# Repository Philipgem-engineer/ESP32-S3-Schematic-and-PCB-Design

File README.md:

# 🧠 ESP32-S3 – Schematic and PCB Design

This repository contains a custom hardware of an ESP32-S3 microcontroller dev board.
It includes the complete schematic and PCB layout, featuring essential supporting circuits.

##  Features
- ⚡ LDO Voltage Regulator – Provides a stable supply for the ESP32-S3 and peripherals
- 🔋 Battery Charging Circuit – Supports rechargeable lithium battery input
- 💾 Flash Memory – Enables program storage capacity
- 🧩 ESP32-S3 System-on-Chip – Dual-core processor with integrated Wi-Fi and Bluetooth
- ⏱️ Crystal Oscillator – Ensures precise clock timing for system stability
- 📡 Antenna & Antenna Matching Circuit – Integrated in PCB for Wi-Fi/Bluetooth connectivity

##  Tools Used
-  Schematic & PCB Design: KiCad
-  Component Library: LCSC
-  PCB Fabrication: JLCPCB

##  Schematic

##  PCB Design

##  PCB 3D view

##  Manufactured PCB

## 📁 File Structure

<details>
  <summary>ESP32-S3 Project/</summary>
  <ul>
    <li>
      Media/
      <ul>
        <li>(PDF, Images and videos of prototype)</li>
      </ul>
    </li>
    <li>
      pcb/
      <ul>
        <li>(Gerber, BOM, Positions)</li>
      </ul>
    </li>
</details>

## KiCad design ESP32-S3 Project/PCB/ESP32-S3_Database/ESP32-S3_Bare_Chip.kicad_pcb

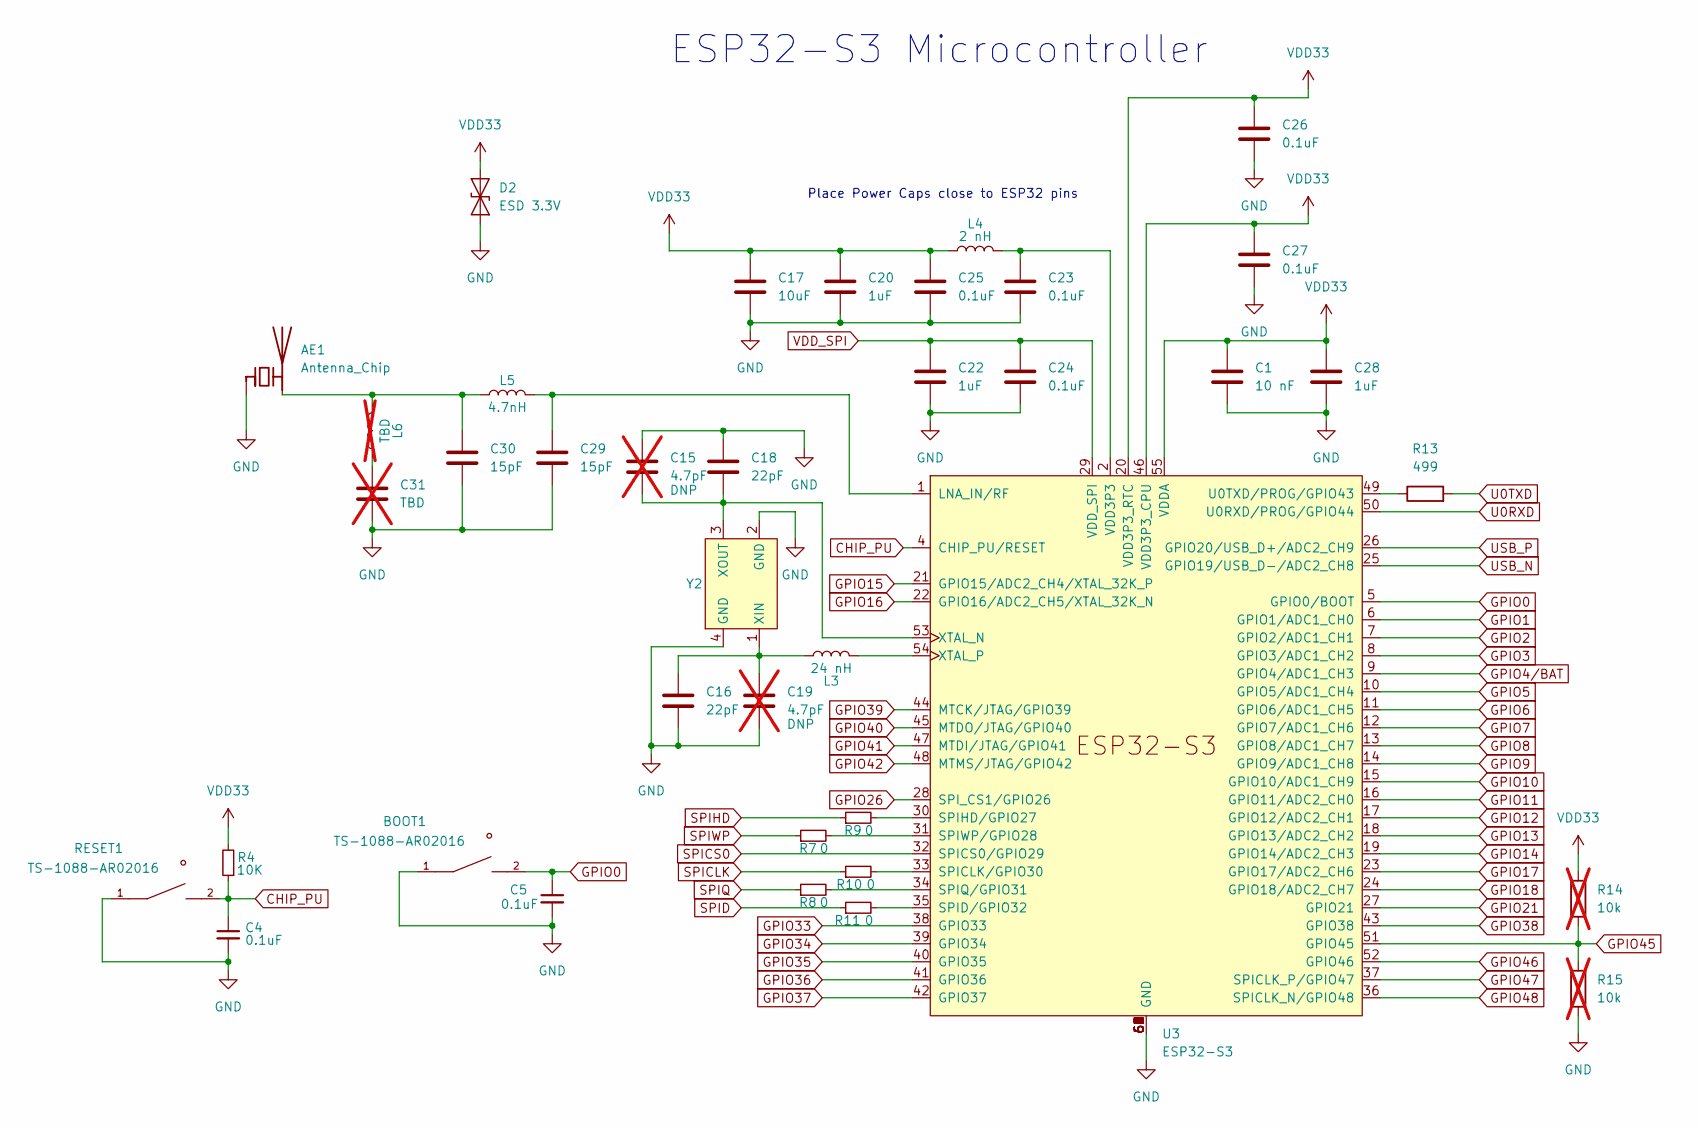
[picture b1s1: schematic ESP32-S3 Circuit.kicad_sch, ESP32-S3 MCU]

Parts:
AE1: Antenna_Chip; Texas_SWRA117D_2.4GHz_Left
BOOT1: TS-1088-AR02016; SW_TS-1088-AR02016; PARTREV N/A
C1: 10 nF; C_0402_1005Metric; MPN CL05B103KB5NNNC
C4, C5, C23, C24, C25, C26, C27: 0.1uF; C_0402_1005Metric; MPN CL05B104KO5NNNC
C15, C19: 4.7pF; C_0402_1005Metric; not fitted
C16, C18: 22pF; C_0402_1005Metric; MPN 0402CG220J500NT
C17: 10uF; C_0402_1005Metric; MPN CL05A106MQ5NUNC
C20, C22, C28: 1uF; C_0402_1005Metric; MPN CL05A105KA5NQNC
C29, C30: 15pF; C_0402_1005Metric; MPN 0402CG220J500NT
C31: TBD; C_0402_1005Metric; MPN 0402CG220J500NT; not fitted
D2: ESD 3.3V; D_SOD-323; MPN H3V3HD3B
L3: 24 nH; L_0402_1005Metric; MPN SDCL1005C24NJTDF
L4: 2 nH; L_0603_1608Metric; MPN SDCL1608C2N0STDF
L5: 4.7nH; L_0402_1005Metric; MPN SDCL1005C4N7STDF
L6: TBD; L_0402_1005Metric; not fitted
R4: 10K; R_0603_1608Metric; MPN 0603WAF1002T5E
R7, R8, R9, R10, R11: 0; R_0402_1005Metric; MPN 0402WGF0000TCE
R13: 499; R_0402_1005Metric; MPN 0402WGF4700TCE
R14, R15: 10k; R_0402_1005Metric; MPN 0402WGF1002TCE; not fitted
RESET1: TS-1088-AR02016; SW_TS-1088-AR02016; PARTREV N/A
U3: ESP32-S3; IC_ESP32-S3; MPN ESP32-S3; LCSC PN C2913192
Y2: Crystal_SMD_3225-4Pin_3.2x2.5mm; MPN 5YMA40000151SF40E1

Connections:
CHIP_PU: C4.1, R4.1, RESET1.2, U3.4 (CHIP_PU/RESET); also elsewhere on the board
GND: AE1.2 (FEED), BOOT1.1, C1.2, C4.2, C5.2, C15.1, C16.2, C17.2, C18.1, C19.2, C20.2, C22.2, C23.2, C24.2, C25.2, C26.2, C27.2, C28.2, C29.2, C30.2, C31.2, D2.1 (A1), R15.1, RESET1.1, U3.57 (GND), U3.58 (GND), U3.59 (GND), U3.60 (GND), U3.61 (GND), U3.62 (GND), U3.63 (GND), U3.64 (GND), U3.65 (GND), U3.66 (GND), U3.67 (GND), U3.68 (GND), U3.69 (GND), Y2.2 (GND), Y2.4 (GND); also elsewhere on the board
GPIO0: BOOT1.2, C5.1, U3.5 (GPIO0/BOOT); also elsewhere on the board
GPIO1: U3.6 (GPIO1/ADC1_CH0); also elsewhere on the board
GPIO2: U3.7 (GPIO2/ADC1_CH1); also elsewhere on the board
GPIO3: U3.8 (GPIO3/ADC1_CH2); also elsewhere on the board
GPIO4/BAT: U3.9 (GPIO4/ADC1_CH3); also elsewhere on the board
GPIO5: U3.10 (GPIO5/ADC1_CH4); also elsewhere on the board
GPIO6: U3.11 (GPIO6/ADC1_CH5); also elsewhere on the board
GPIO7: U3.12 (GPIO7/ADC1_CH6); also elsewhere on the board
GPIO8: U3.13 (GPIO8/ADC1_CH7); also elsewhere on the board
GPIO9: U3.14 (GPIO9/ADC1_CH8); also elsewhere on the board
GPIO10: U3.15 (GPIO10/ADC1_CH9); also elsewhere on the board
GPIO11: U3.16 (GPIO11/ADC2_CH0); also elsewhere on the board
GPIO12: U3.17 (GPIO12/ADC2_CH1); also elsewhere on the board
GPIO13: U3.18 (GPIO13/ADC2_CH2); also elsewhere on the board
GPIO14: U3.19 (GPIO14/ADC2_CH3); also elsewhere on the board
GPIO15: U3.21 (GPIO15/ADC2_CH4/XTAL_32K_P); also elsewhere on the board
GPIO16: U3.22 (GPIO16/ADC2_CH5/XTAL_32K_N); also elsewhere on the board
GPIO17: U3.23 (GPIO17/ADC2_CH6); also elsewhere on the board
GPIO18: U3.24 (GPIO18/ADC2_CH7); also elsewhere on the board
GPIO21: U3.27 (GPIO21); also elsewhere on the board
GPIO26: U3.28 (SPI_CS1/GPIO26); also elsewhere on the board
GPIO33: U3.38 (GPIO33); also elsewhere on the board
GPIO34: U3.39 (GPIO34); also elsewhere on the board
GPIO35: U3.40 (GPIO35); also elsewhere on the board
GPIO36: U3.41 (GPIO36); also elsewhere on the board
GPIO37: U3.42 (GPIO37); also elsewhere on the board
GPIO38: U3.43 (GPIO38); also elsewhere on the board
GPIO39: U3.44 (MTCK/JTAG/GPIO39); also elsewhere on the board
GPIO40: U3.45 (MTDO/JTAG/GPIO40); also elsewhere on the board
GPIO41: U3.47 (MTDI/JTAG/GPIO41); also elsewhere on the board
GPIO42: U3.48 (MTMS/JTAG/GPIO42); also elsewhere on the board
GPIO45: R14.1, R15.2, U3.51 (GPIO45); also elsewhere on the board
GPIO46: U3.52 (GPIO46); also elsewhere on the board
GPIO47: U3.37 (SPICLK_P/GPIO47); also elsewhere on the board
GPIO48: U3.36 (SPICLK_N/GPIO48); also elsewhere on the board
unnamed: AE1.1 (PCB_Trace), C30.1, L5.1, L6.2
unnamed: C31.1, L6.1
unnamed: C29.1, L5.2, U3.1 (LNA_IN/RF)
unnamed: R10.2, U3.33 (SPICLK/GPIO30)
unnamed: R11.2, U3.35 (SPID/GPIO32)
unnamed: R9.2, U3.30 (SPIHD/GPIO27)
unnamed: R8.2, U3.34 (SPIQ/GPIO31)
unnamed: R7.2, U3.31 (SPIWP/GPIO28)
unnamed: R13.1, U3.49 (U0TXD/PROG/GPIO43)
unnamed: C15.2, C18.2, U3.53 (XTAL_N), Y2.3 (XOUT)
unnamed: L3.2, U3.54 (XTAL_P)
unnamed: C16.1, C19.1, L3.1, Y2.1 (XIN)
SPICLK: R10.1; also elsewhere on the board
SPICS0: U3.32 (SPICS0/GPIO29); also elsewhere on the board
SPID: R11.1; also elsewhere on the board
SPIHD: R9.1; also elsewhere on the board
SPIQ: R8.1; also elsewhere on the board
SPIWP: R7.1; also elsewhere on the board
U0RXD: U3.50 (U0RXD/PROG/GPIO44); also elsewhere on the board
U0TXD: R13.2; also elsewhere on the board
USB_N: U3.25 (GPIO19/USB_D-/ADC2_CH8); also elsewhere on the board
USB_P: U3.26 (GPIO20/USB_D+/ADC2_CH9); also elsewhere on the board
VDD3P3: C23.1, L4.2, U3.2 (VDD3P3), U3.3 (VDD3P3)
VDD33: C1.1, C17.1, C20.1, C25.1, C26.1, C27.1, C28.1, D2.2 (A2), L4.1, R4.2, R14.2, U3.20 (VDD3P3_RTC), U3.46 (VDD3P3_CPU), U3.55 (VDDA), U3.56 (VDDA); also elsewhere on the board
VDD_SPI: C22.1, C24.1, U3.29 (VDD_SPI); also elsewhere on the board

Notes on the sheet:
Place Power Caps close to ESP32 pins
ESP32-S3 Microcontroller

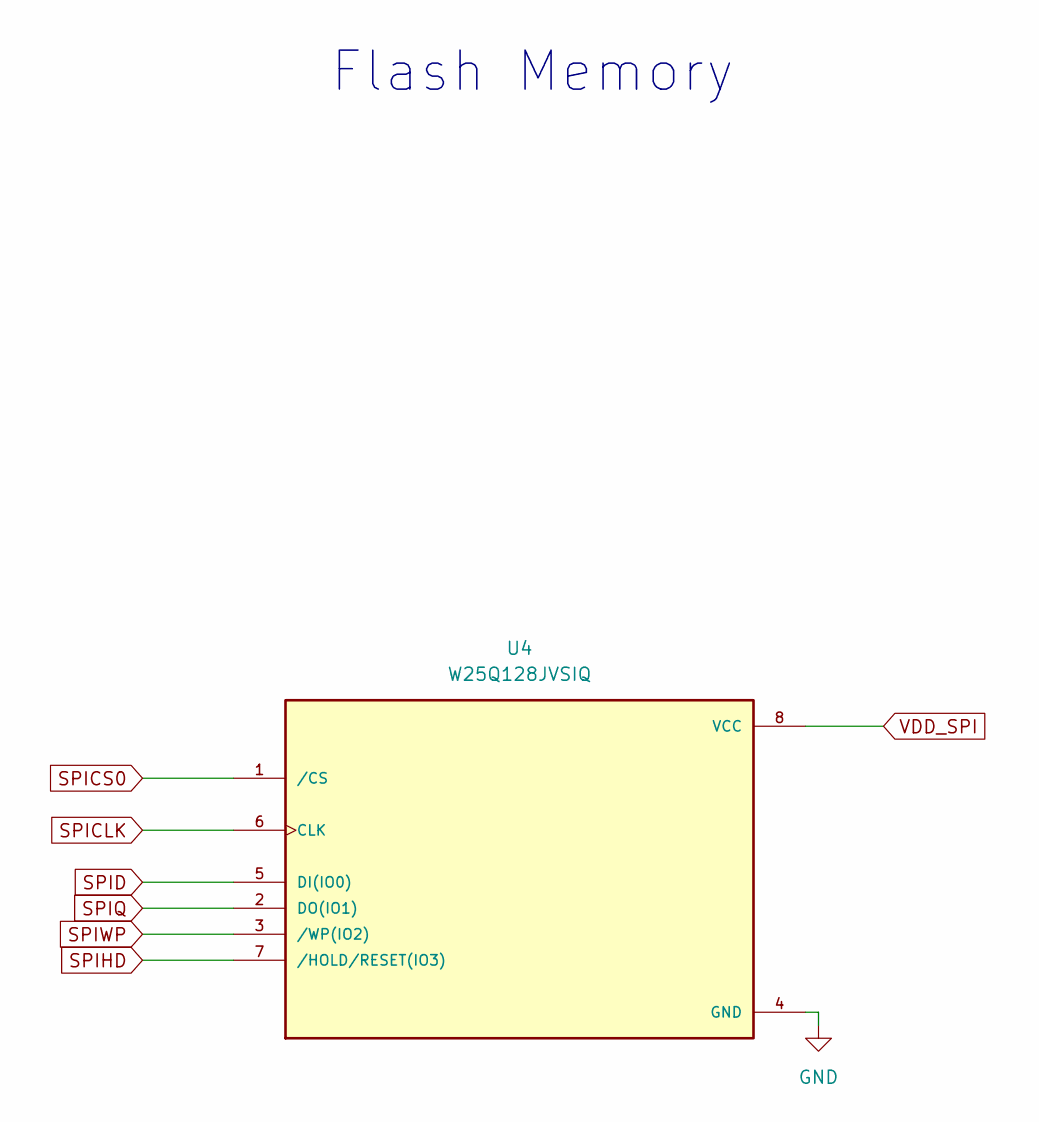
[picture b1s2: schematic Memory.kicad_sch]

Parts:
U4: W25Q128JVSIQ; SOIC127P790X216-8N; PARTREV I

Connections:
GND: U4.4 (GND); also elsewhere on the board
SPICLK: U4.6 (CLK); also elsewhere on the board
SPICS0: U4.1 (/CS); also elsewhere on the board
SPID: U4.5 (DI(IO0)); also elsewhere on the board
SPIHD: U4.7 (/HOLD/RESET(IO3)); also elsewhere on the board
SPIQ: U4.2 (DO(IO1)); also elsewhere on the board
SPIWP: U4.3 (/WP(IO2)); also elsewhere on the board
VDD_SPI: U4.8 (VCC); also elsewhere on the board

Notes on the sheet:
Flash Memory

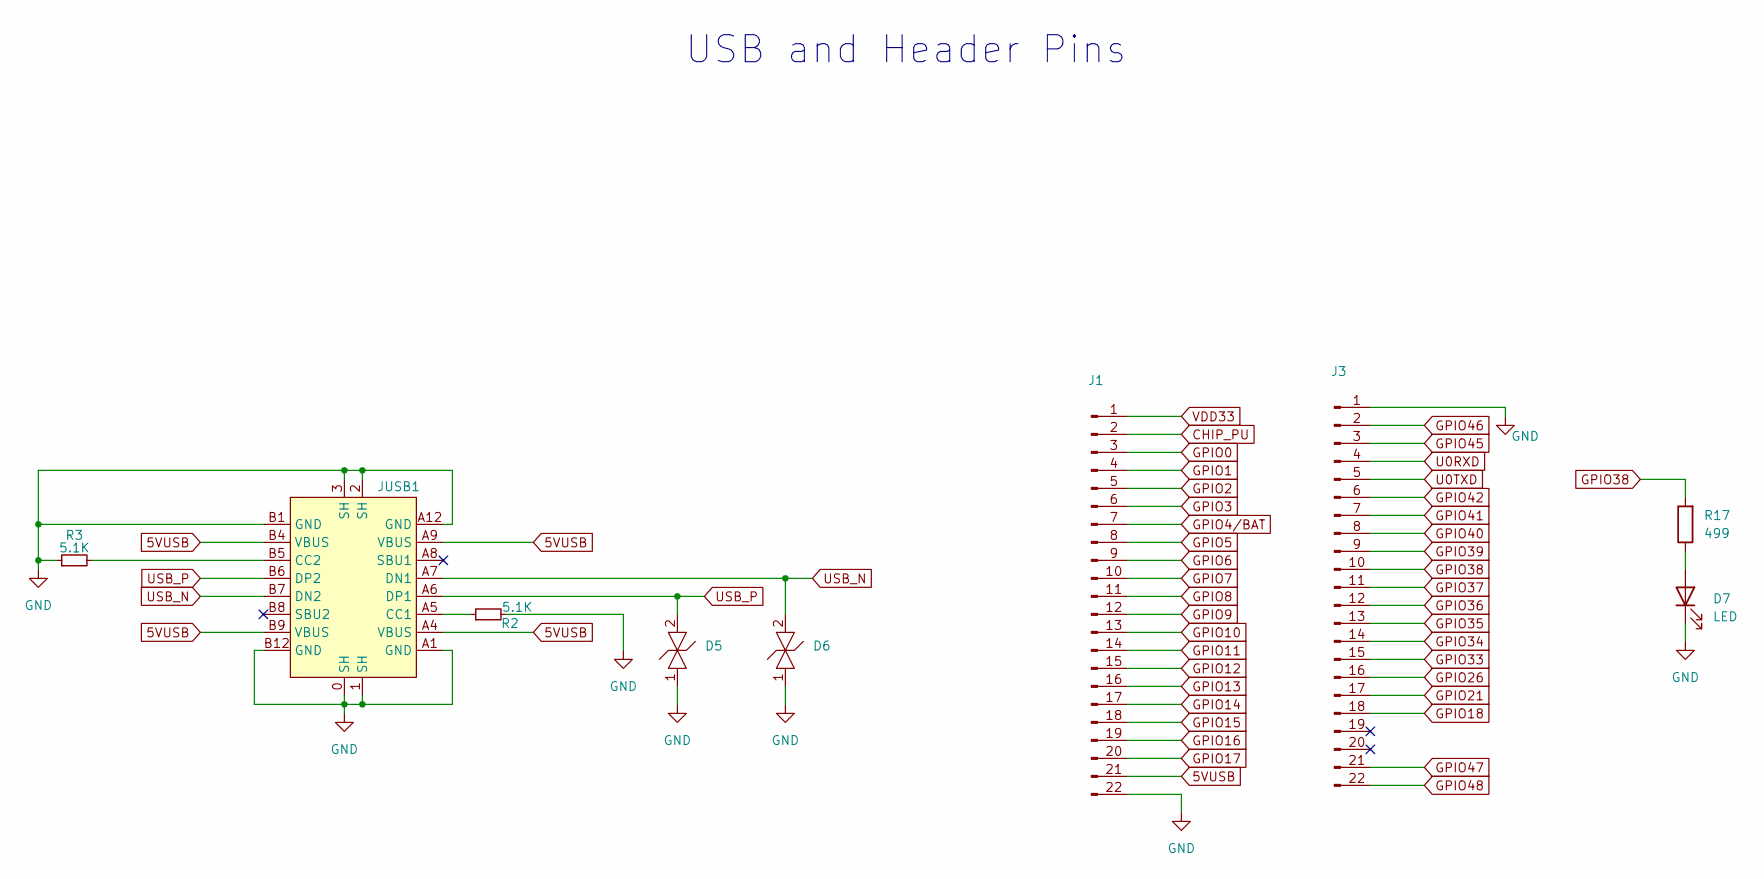
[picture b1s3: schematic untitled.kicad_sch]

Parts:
D5, D6: H5VL10B; MPN H5VL10B
D7: LED; LED_0603_1608Metric; MPN KT-0603R
J1, J3: PinHeader_1x22_P2.54mm_Vertical
JUSB1: USB_TYPE_18; MPN DEALON USB-TYPE-C-018
R2, R3: 5.1K; R_0603_1608Metric; MPN 0603WAF5101T5E
R17: 499; R_0402_1005Metric; MPN 0402WGF4700TCE

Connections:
5VUSB: J1.21, JUSB1.A4 (VBUS), JUSB1.A9 (VBUS), JUSB1.B4 (VBUS), JUSB1.B9 (VBUS); also elsewhere on the board
CHIP_PU: J1.2; also elsewhere on the board
GND: D5.1, D6.1, D7.1 (K), J1.22, J3.1, JUSB1.0 (SH), JUSB1.1 (SH), JUSB1.2 (SH), JUSB1.3 (SH), JUSB1.A1 (GND), JUSB1.A12 (GND), JUSB1.B1 (GND), JUSB1.B12 (GND), R2.2, R3.1; also elsewhere on the board
GPIO0: J1.3; also elsewhere on the board
GPIO1: J1.4; also elsewhere on the board
GPIO2: J1.5; also elsewhere on the board
GPIO3: J1.6; also elsewhere on the board
GPIO4/BAT: J1.7; also elsewhere on the board
GPIO5: J1.8; also elsewhere on the board
GPIO6: J1.9; also elsewhere on the board
GPIO7: J1.10; also elsewhere on the board
GPIO8: J1.11; also elsewhere on the board
GPIO9: J1.12; also elsewhere on the board
GPIO10: J1.13; also elsewhere on the board
GPIO11: J1.14; also elsewhere on the board
GPIO12: J1.15; also elsewhere on the board
GPIO13: J1.16; also elsewhere on the board
GPIO14: J1.17; also elsewhere on the board
GPIO15: J1.18; also elsewhere on the board
GPIO16: J1.19; also elsewhere on the board
GPIO17: J1.20; also elsewhere on the board
GPIO18: J3.18; also elsewhere on the board
GPIO21: J3.17; also elsewhere on the board
GPIO26: J3.16; also elsewhere on the board
GPIO33: J3.15; also elsewhere on the board
GPIO34: J3.14; also elsewhere on the board
GPIO35: J3.13; also elsewhere on the board
GPIO36: J3.12; also elsewhere on the board
GPIO37: J3.11; also elsewhere on the board
GPIO38: J3.10, R17.2; also elsewhere on the board
GPIO39: J3.9; also elsewhere on the board
GPIO40: J3.8; also elsewhere on the board
GPIO41: J3.7; also elsewhere on the board
GPIO42: J3.6; also elsewhere on the board
GPIO45: J3.3; also elsewhere on the board
GPIO46: J3.2; also elsewhere on the board
GPIO47: J3.21; also elsewhere on the board
GPIO48: J3.22; also elsewhere on the board
unnamed: D7.2 (A), R17.1
unnamed: JUSB1.A5 (CC1), R2.1
unnamed: JUSB1.B5 (CC2), R3.2
U0RXD: J3.4; also elsewhere on the board
U0TXD: J3.5; also elsewhere on the board
USB_N: D6.2, JUSB1.A7 (DN1), JUSB1.B7 (DN2); also elsewhere on the board
USB_P: D5.2, JUSB1.A6 (DP1), JUSB1.B6 (DP2); also elsewhere on the board
VDD33: J1.1; also elsewhere on the board

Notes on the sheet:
USB and Header Pins

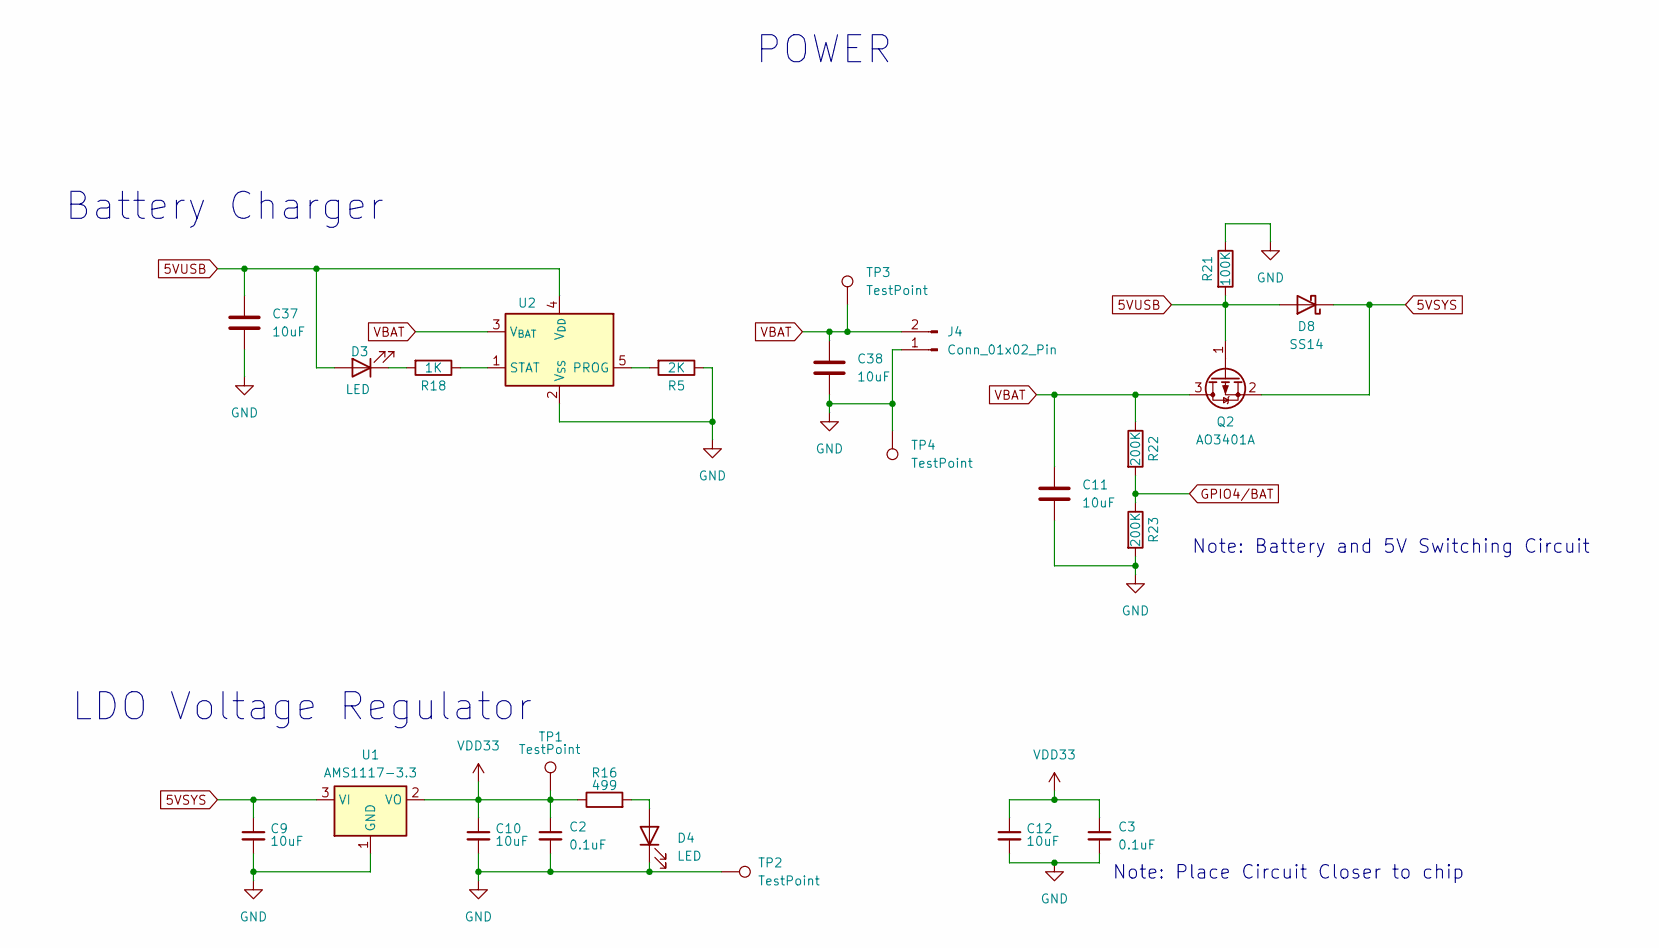
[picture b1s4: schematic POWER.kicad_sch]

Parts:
C2, C3: 0.1uF; C_0402_1005Metric; MPN CL05B104KO5NNNC
C9, C10, C12: 10uF; C_0402_1005Metric; MPN CL05A106MQ5NUNC
C11, C37, C38: 10uF; C_0402_1005Metric; MNF PART NUMBER C15525; LCSC C15525
D3: LED; LED_0603_1608Metric; MNF PART NUMBER C2286; LCSC C2286
D4: LED; LED_0603_1608Metric; MPN KT-0603R
D8: SS14; D_SMA; MNF PART NUMBER C2480; LCSC C2480
J4: Conn_01x02_Pin; PinSocket_1x02_P2.54mm_Vertical
Q2: AO3401A; SOT-23; MNF PART NUMBER C15127; LCSC C15127
R5: 2K; R_0402_1005Metric; MNF PART NUMBER C4109; LCSC C4109
R16: 499; R_0402_1005Metric; MPN 0402WGF4700TCE
R18: 1K; R_0402_1005Metric; MNF PART NUMBER C11702; LCSC C11702
R21: 100K; R_0402_1005Metric; MNF PART NUMBER C25741; LCSC C25741
R22, R23: 200K; R_0402_1005Metric; MNF PART NUMBER C25764; LCSC C25764
TP1, TP2, TP3, TP4: TestPoint; TestPoint_Pad_D1.0mm
U1: AMS1117-3.3; SOT-223-3_TabPin2; MPN AMS1117-3.3
U2: SOT-23-5; MPN TP4054-42-SOT25R

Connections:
5VSYS: C9.1, D8.1 (K), Q2.2 (S), U1.3 (VI)
5VUSB: C37.1, D3.2 (A), D8.2 (A), Q2.1 (G), R21.2, U2.4 (V_{DD}); also elsewhere on the board
GND: C2.2, C3.2, C9.2, C10.2, C11.2, C12.2, C37.2, C38.2, D4.1 (K), J4.1, R5.1, R21.1, R23.2, TP2.1, TP4.1, U1.1 (GND), U2.2 (V_{SS}); also elsewhere on the board
GPIO4/BAT: R22.2, R23.1; also elsewhere on the board
unnamed: D3.1 (K), R18.2
unnamed: D4.2 (A), R16.2
unnamed: R5.2, U2.5 (PROG)
unnamed: R18.1, U2.1 (STAT)
VBAT: C11.1, C38.1, J4.2, Q2.3 (D), R22.1, TP3.1, U2.3 (V_{BAT})
VDD33: C2.1, C3.1, C10.1, C12.1, R16.1, TP1.1, U1.2 (VO); also elsewhere on the board

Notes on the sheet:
LDO Voltage Regulator
Note: Place Circuit Closer to chip
Note: Battery and 5V Switching Circuit
POWER
Battery Charger

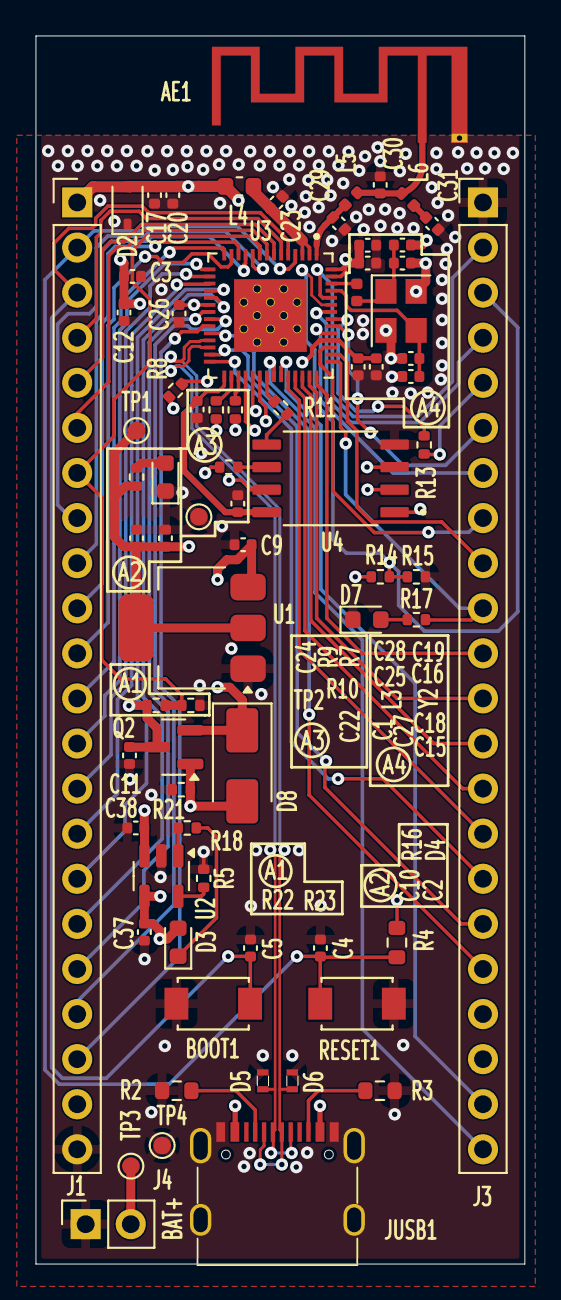
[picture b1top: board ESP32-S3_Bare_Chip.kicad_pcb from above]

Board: 4 copper layers, 27.5 x 69.2 mm, 73 parts (0 on the bottom side), 72 nets.

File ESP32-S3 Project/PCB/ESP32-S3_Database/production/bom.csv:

Designator,Footprint,Quantity,Value,LCSC Part #
AE1,Texas_SWRA117D_2.4GHz_Left,1,Antenna_Chip,
"BOOT1, RESET1",SW_TS-1088-AR02016,2,TS-1088-AR02016,TS-1088-AR02016 
C1,0402,1,10 nF,CL05B103KB5NNNC 
"C10, C12, C9",0402,3,10uF,CL05A106MQ5NUNC
"C11, C37, C38",0402,3,10uF,C15525
"C16, C18",0402,2,22pF,0402CG220J500NT
C17,0402,1,10uF, CL05A106MQ5NUNC
"C2, C3",0402,2,0.1uF,CL05B104KO5NNNC
C20,0402,1,1uF,CL05A105KA5NQNC
"C22, C28",0402,2,1uF,CL05A105KA5NQNC 
"C23, C24, C25, C26, C27",0402,5,0.1uF, CL05B104KO5NNNC
"C29, C30",0402,2,15pF,0402CG220J500NT
"C4, C5",0402,2,0.1uF,CL05B104KO5NNNC 
D2,D_SOD-323,1,ESD 3.3V, H3V3HD3B
D3,0603,1,LED,C2286
"D4, D7",0603,2,LED,KT-0603R
"D5, D6",H5VL10B,2,~,H5VL10B
D8,D_SMA,1,SS14,C2480
"J1, J3",PinHeader_1x22_P2.54mm_Vertical,2,~,
J4,PinSocket_1x02_P2.54mm_Vertical,1,Conn_01x02_Pin,
JUSB1,USB_TYPE_18,1,~,DEALON USB-TYPE-C-018 
L3,0402,1,24 nH,SDCL1005C24NJTDF
L4,0603,1,2 nH,SDCL1608C2N0STDF 
L5,0402,1,4.7nH,SDCL1005C4N7STDF
Q2,SOT-23,1,AO3401A,C15127
"R10, R11, R7, R8, R9",0402,5,0,0402WGF0000TCE
R13,0402,1,499,0402WGF4700TCE
"R16, R17",0402,2,499,0402WGF4700TCE 
R18,0402,1,1K,C11702
"R2, R3",0603,2,5.1K,0603WAF5101T5E
R21,0402,1,100K,C25741
"R22, R23",0402,2,200K,C25764
R4,0603,1,10K,0603WAF1002T5E 
R5,0402,1,2K,C4109
"TP1, TP2, TP3, TP4",TestPoint_Pad_D1.0mm,4,TestPoint,
U1,SOT-223-3_TabPin2,1,AMS1117-3.3,AMS1117-3.3
U2,SOT-23-5,1,~,TP4054-42-SOT25R 
U3,IC_ESP32-S3,1,ESP32-S3,C2913192
U4,SOIC127P790X216-8N,1,W25Q128JVSIQ,W25Q128JVSIQ
Y2,Crystal_SMD_3225-4Pin_3.2x2.5mm,1,~,5YMA40000151SF40E1
